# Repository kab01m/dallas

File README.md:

## DV-87-12 is a replacement module for Dallas DS1287

This project is a complete replacement of widely used RTC modules DS1287, DS12887, DS12887+ originally made by Dallas and their derivatives.

Contents of this repository may be freely used for any purpose including PCB manufacturing and product selling with original copyright marking. DV-87-12 and DV-87-12R were made in DipTrace and DV-87-12SR was made in KiCad EDA 8.0.

### Options

#### Boards

These are variants of boards using different IC footprint and battery holder:

* DV-87-12:
    * B1 is BS-1220-2 battery holder.
    * U1 is SOIC 300-mil (DS12885S, DS12885S+, bq3285, bq4285).
* DV-87-12R:
    * B1 is Renata SMTU-1225-LF battery holder.
    * U1 is SOIC 300-mil (DS12885S, DS12885S+, bq3285, bq4285).
* DV-87-12SR:
    * B1 is Renata SMTU-1225-LF battery holder.
    * U1 is SSOP 150-mil (bq3285LF).
    * Unfortunately, this board can't be used for bq4285 or DS1387.

#### R1/R2/R3

Only one of R1, R2 and R3 should be installed. DS1287 pin 1 is a mode select, some motherboards do not have it working, so you can pull pin 1 up with R2 for Motorola mode or down with R3 for Intel mode. Put zero resistor in R1 if you do not know.

#### R4/R5

Original DS1287 have 21 and 22 as not-connected, so by default you do not install R4 and R5. Some motherboards are known to use RCLR signal on pin 21, so you have to put zero resitor into R4 if it does not work right. DS13* or DS14* are using both 21 and 22 pins, so you put both R4 and R5 in place.

#### U1

You can use DS12885, bq3285 or bq4285 depending on what you can find and what original chip you want to replace.

* DS1287 series:
    * Dallas DS1287, DS12887, DS12B887 : bq3285, DS12885S or S+, use R1.
    * Dallas DS12C887, DS12887+ : bq3285 or DS12885S+, use R1 and R4.
    * ST M48T86PC1 : bq3285 or DS12885S+, use R1 and R4.
    * Benchmarq BQ3287 : bq3285, use R1, R4.
    * ODIN OEC12C887 : bq3285, DS12885S or S+, use R1.
    * VIA VT82887 : bq3285, DS12885S or S+, use R1.
* DS1387 series
    * Dallas DS1387 : DS1385, use R1, R4, R5.
* DS1487 series
    * Dallas DS14287 : bq4285, use R1, R4, R5.
    * Benchmarq BQ4287 : bq4285, use R1, R4, R5.
* Motorola MC146818A can be supported. Tell me if you need it.

### Bill of Materials

* DV-87-12 PCB board, use supplied Gerbers.
* U1 - DS12885, bq3285, bq4285 or DS1385 (see above).
* B1 - BS-1220-2 or SMTU-1225-LF.
* B1 - CR1225 3V lithium cell
* Y1 - 32.768 kHz crystal, 3215 metric SMD.
* R1 - Zero 0805 inch SMD to enable selector mode (default).
* R2 - 10 K 0805 inch SMD to enable Motorola mode (optional).
* R3 - 10 K 0805 inch SMD to enable Intel mode (optional).
* R4 - Zero 0805 inch SMD for 21 pin (optional).
* R5 - Zero 0805 inch SMD for 22 pin (optional).

### Useful links

* [Necrowave project](https://github.com/necroware/nwX287) for replacing Dallas RTC.
* [Glitchworks](https://github.com/glitchwrks) have GW-1287-1 module, but did not publish sources.

None of these were used in that project.

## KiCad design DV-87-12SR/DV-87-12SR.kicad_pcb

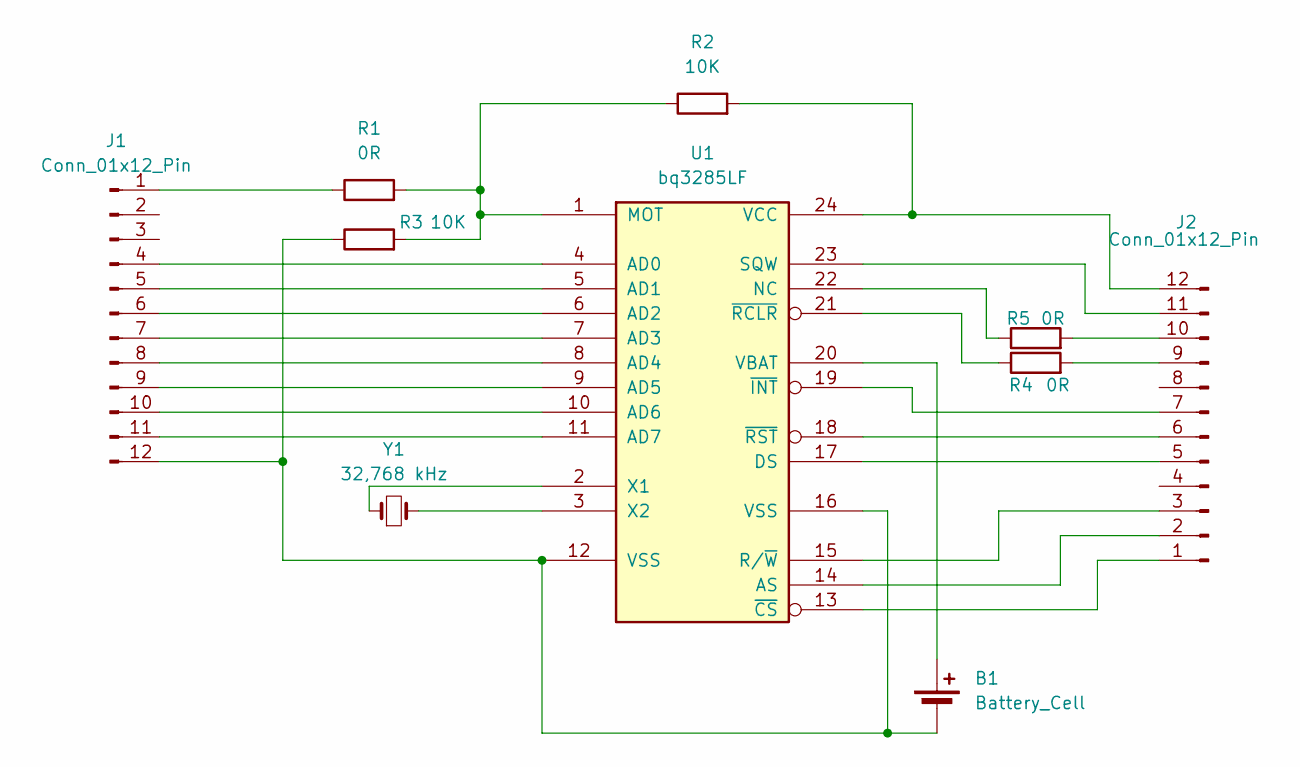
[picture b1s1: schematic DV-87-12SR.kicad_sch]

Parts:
B1: Battery_Cell; BatteryHolder_Renata_SMTU1225-LF_1x1225
J1, J2: Conn_01x12_Pin; PinHeader_1x12_P2.54mm_Vertical
R1, R4, R5: 0R; R_0805_2012Metric
R2, R3: 10K; R_0805_2012Metric
U1: bq3285LF; SSOP-24_3.9x8.7mm_P0.635mm
Y1: 32,768 kHz; Crystal_SMD_3215-2Pin_3.2x1.5mm

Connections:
unnamed: B1.1 (+), U1.20 (VBAT)
unnamed: B1.2 (-), J1.12, R3.1, U1.12 (VSS), U1.16 (VSS)
unnamed: J1.1, R1.1
unnamed: J1.4, U1.4 (AD0)
unnamed: J1.5, U1.5 (AD1)
unnamed: J1.6, U1.6 (AD2)
unnamed: J1.7, U1.7 (AD3)
unnamed: J1.8, U1.8 (AD4)
unnamed: J1.9, U1.9 (AD5)
unnamed: J1.10, U1.10 (AD6)
unnamed: J1.11, U1.11 (AD7)
unnamed: J2.1, U1.13 (~CS)
unnamed: J2.2, U1.14 (AS)
unnamed: J2.3, U1.15 (R/~W)
unnamed: J2.5, U1.17 (DS)
unnamed: J2.6, U1.18 (~RST)
unnamed: J2.7, U1.19 (~INT)
unnamed: J2.9, R4.2
unnamed: J2.10, R5.2
unnamed: J2.11, U1.23 (SQW)
unnamed: J2.12, R2.2, U1.24 (VCC)
unnamed: R1.2, R2.1, R3.2, U1.1 (MOT)
unnamed: R5.1, U1.22 (NC)
unnamed: U1.2 (X1), Y1.1
unnamed: U1.3 (X2), Y1.2
unnamed: R4.1, U1.21 (~RCLR)

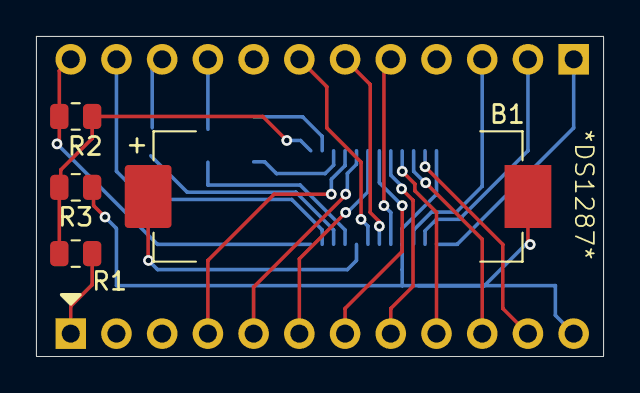
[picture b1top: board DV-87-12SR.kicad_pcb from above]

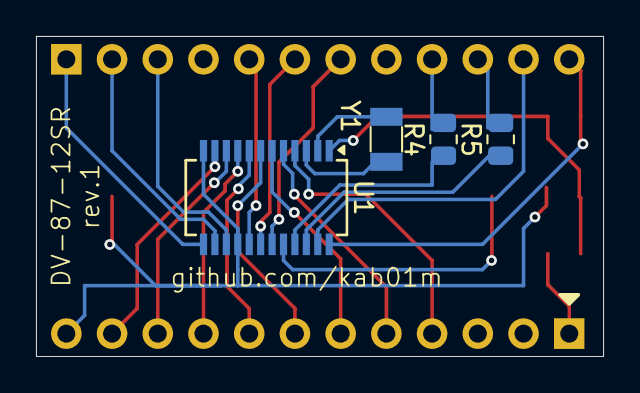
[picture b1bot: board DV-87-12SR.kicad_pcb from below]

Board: 2 copper layers, 31.5 x 17.8 mm, 10 parts (4 on the bottom side), 26 nets.

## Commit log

2024-03-17 License fix
2024-03-17 Add Renata version
2024-03-17 Small fix and additional info
2024-03-17 Letter fix
2024-03-18 Add SR variant
